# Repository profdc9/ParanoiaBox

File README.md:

# ParanoiaBox
The ParanoiaBox by Daniel L. Marks

The ParanoiaBox is a standalone open hardware/software encryption device based on the STM32F103CBT6 processor.  On this device, messages may be composed, encrypted, decrypted, and viewed.  The device is an experiment in encryption minimalism, presenting a minimal attack surface by using a small microcontroller rather than a full personal computer with a complex operating system, while providing the functionality needed to transact encrypted messages between humans through insecure networks.  The device is connected to a NTSC television and a PS/2 keyboard for user input and control.  There are two micro SD card slots, one for ciphertext and the other for plaintext used to transact files.  There is a hardware random number generator based on avalanche noise generated in two transistors.  A picture of the complete PCB of the device can be seen below:

At the top of the board is a RCA composite video connector.  At the right is a USB B connector that can be used to program the microcontroller.  At the lower right is a female PS/2 keyboard connector.  At the bottom are two SD card slots.  Finally, at the left is a barrel jack for 7 to 12 volt DC input power.  Except for the micro SD card slots, the PCB is all through assembly so it can be assembled more easily using simple tools.

The hardware is licensed under the Creative Commons CC-BY-SA 4.0 license.  The software written by D. L. Marks is licensed under the zlib license.  All other libraries are licensed under the licenses as described in the corresponding source files.  This hardware and software is provided under these licenses to be used at your own risk.  

THE HARDWARE AND SOFTWARE IS PROVIDED "AS IS", WITHOUT WARRANTY OF ANY KIND, EXPRESS OR IMPLIED, INCLUDING BUT NOT LIMITED TO THE WARRANTIES OF MERCHANTABILITY, FITNESS FOR A PARTICULAR PURPOSE AND NONINFRINGEMENT. IN NO EVENT SHALL THE AUTHORS OR COPYRIGHT HOLDERS BE LIABLE FOR ANY CLAIM, DAMAGES OR OTHER LIABILITY, WHETHER IN AN ACTION OF CONTRACT, TORT OR OTHERWISE, ARISING FROM, OUT OF OR IN CONNECTION WITH THE HARDWARE AND SOFTWARE OR THE USE OR OTHER DEALINGS IN THE HARDWARE AND SOFTWARE.

The project uses Advanced Encryption Standard AES256-GCM Galois Counter Mode as an authenticated symmetric encryption.  The keys are derived from shared secrets based on then Elliptic Curve Diffie-Hellmann (ECDH) 25519.  The keys are encrypted using a passphrase and AES256-GCM and stored in the flash memory of the microcontroller.  The encrypted data and public key certificates are base64 encoded so that they can be transmitted through e-mail as text files.  The library used is the Arduino Cryptography Library by Rhys Weatherley:

https://rweather.github.io/arduinolibs/crypto.html

The project uses the stm32duino libraries located here:

https://github.com/rogerclarkmelbourne/Arduino_STM32

All other Arduino libraries are provided in the libraries directory in this project, including those that provide the FAT fs, NTSC video output, PS/2 keyboard input, and cryptography.  To enter a message into the microcontroller, there is a full-screen text editor:

There is a the built-in full-screen editor used to compose short messages.  Files may be selected from the SD cards for editing, encryption, or decryption:

This is the key manager screen from which the AES 256 symmetric, ECDH25519 private or public keys are selected:

To encrypt/decrypt using AES, a AES key is selected.  To encrypt/decrypt using ECDH25519, a private and public key pair are selected.   Then one selects a file to encrypt or decrypt.  Separate SD cards must be used for encryption and decryption to ensure that both are not available together to be compared.  One can export a public key certificate from a private key.  After selection, the main screen shows the selected keys:

The message is then encrypted by selecting the file from the card in the plaintext slot using the (E)ncrypt option.  Then the encrypted file is placed on the card in the ciphertext slot.  You can view this file which is text encoded to be easily transmitted over email:

Once it has been received, it can be decrypted and viewed, and it looks like the original:

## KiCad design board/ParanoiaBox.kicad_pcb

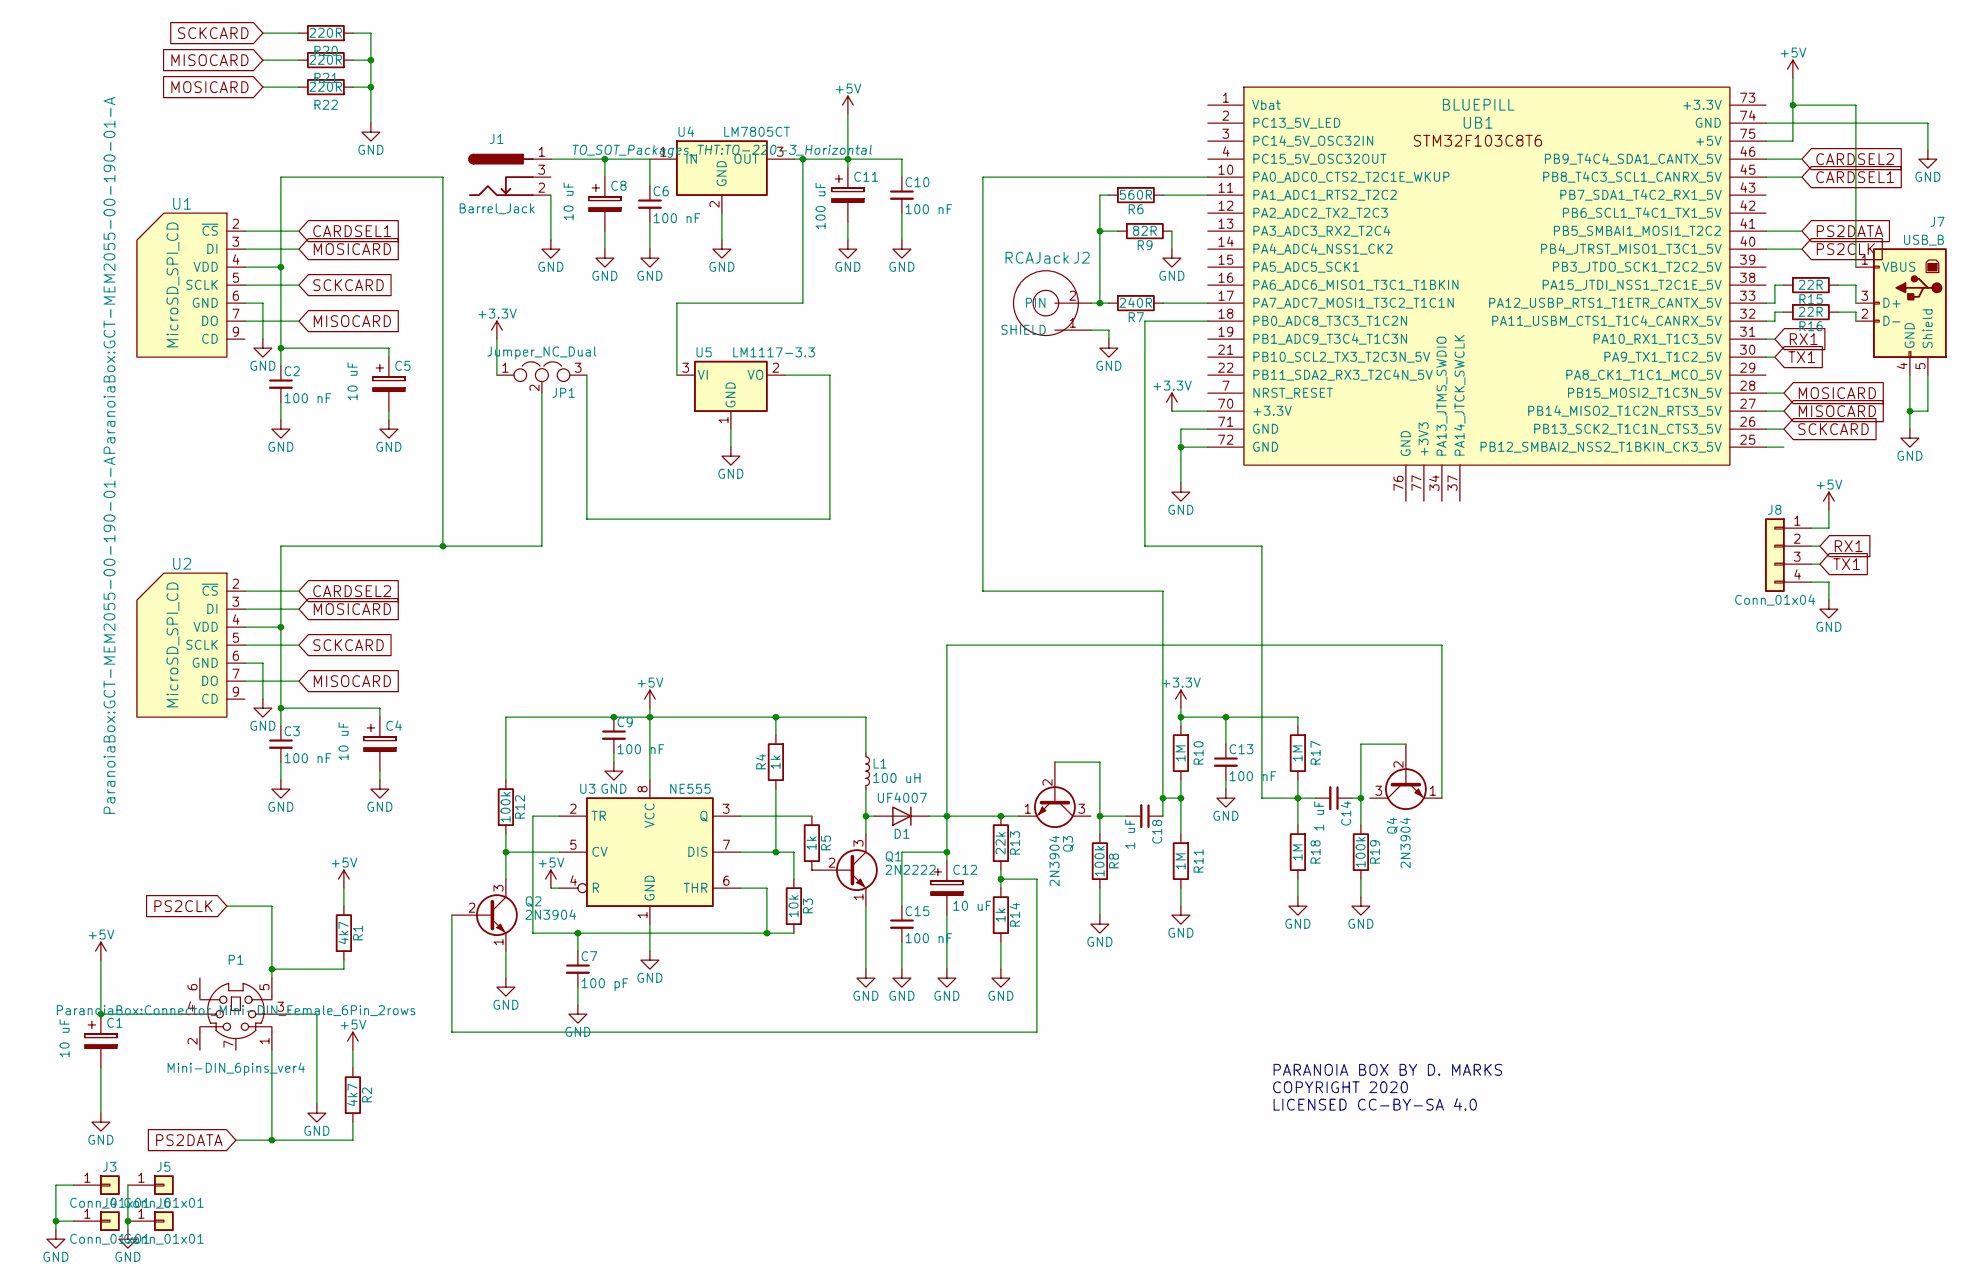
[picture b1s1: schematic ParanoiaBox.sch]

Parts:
C1, C4, C5, C8, C12: 10 uF; CP_Radial_D5.0mm_P2.50mm
C2, C3, C6, C9, C10, C13, C15: 100 nF; C_Disc_D5.0mm_W2.5mm_P2.50mm
C7: 100 pF; C_Disc_D5.0mm_W2.5mm_P2.50mm
C11: 100 uF; CP_Radial_D10.0mm_P5.00mm
C14, C18: 1 uF; C_Disc_D5.0mm_W2.5mm_P5.00mm
D1: UF4007; D_DO-41_SOD81_P7.62mm_Horizontal
J1: Barrel_Jack; BARREL_JACK
J2: RCAJack; RCAConnectorCommon
J3, J4, J5, J6: Conn_01x01; 1pin
J7: USB_B
J8: Conn_01x04; Pin_Header_Straight_1x04_Pitch2.54mm
JP1: Jumper_NC_Dual; Pin_Header_Straight_1x03_Pitch2.54mm
L1: 100 uH; L_Toroid_Horizontal_D5.1mm_P9.00mm_Diameter6-5mm_Amidon-T20
P1: Mini-DIN_6pins_ver4; Connector_Mini-DIN_Female_6Pin_2rows
Q1: 2N2222; TO-92_Inline_Wide
Q2, Q3, Q4: 2N3904; TO-92_Inline_Wide
R1, R2: 4k7; R_Axial_DIN0207_L6.3mm_D2.5mm_P7.62mm_Horizontal
R3: 10k; R_Axial_DIN0207_L6.3mm_D2.5mm_P7.62mm_Horizontal
R4, R5, R14: 1k; R_Axial_DIN0207_L6.3mm_D2.5mm_P7.62mm_Horizontal
R6: 560R; R_Axial_DIN0207_L6.3mm_D2.5mm_P7.62mm_Horizontal
R7: 240R; R_Axial_DIN0207_L6.3mm_D2.5mm_P7.62mm_Horizontal
R8, R12, R19: 100k; R_Axial_DIN0207_L6.3mm_D2.5mm_P7.62mm_Horizontal
R9: 82R; R_Axial_DIN0207_L6.3mm_D2.5mm_P7.62mm_Horizontal
R10, R11, R17, R18: 1M; R_Axial_DIN0207_L6.3mm_D2.5mm_P7.62mm_Horizontal
R13: 22k; R_Axial_DIN0207_L6.3mm_D2.5mm_P7.62mm_Horizontal
R15, R16: 22R; R_Axial_DIN0207_L6.3mm_D2.5mm_P7.62mm_Horizontal
R20, R21, R22: 220R; R_Axial_DIN0207_L6.3mm_D2.5mm_P7.62mm_Horizontal
U1, U2: MicroSD_SPI_CD; GCT-MEM2055-00-190-01-A
U3: NE555; DIP-8_W7.62mm_Socket
U4: LM7805CT; TO-220-3_Horizontal
U5: LM1117-3.3; TO-220-3_Horizontal
UB1: BLUEPILL

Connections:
+3V3: C13.1, JP1.1, R10.2, R17.2, UB1.70 (+3.3V)
+5V: C1.1, C9.1, C10.1, C11.1, J7.1 (VBUS), J8.1, L1.1, P1.4, R1.1, R2.1, R4.2, R12.1, U3.4 (R), U3.8 (VCC), U4.3 (OUT), U5.3 (VI), UB1.75 (+5V)
CARDSEL1: U1.2 (~CS), UB1.45 (PB8_T4C3_SCL1_CANRX_5V)
CARDSEL2: U2.2 (~CS), UB1.46 (PB9_T4C4_SDA1_CANTX_5V)
GND: C1.2, C2.2, C3.2, C4.2, C5.2, C6.2, C7.2, C8.2, C9.2, C10.2, C11.2, C12.2, C13.2, C15.2, J1.2, J2.1 (SHIELD), J3.1, J4.1, J5.1, J6.1, J7.4 (GND), J7.5 (Shield), J8.4, P1.3, Q1.1 (E), Q2.1 (E), R8.2, R9.1, R11.1, R14.2, R18.1, R19.2, R20.2, R21.2, R22.2, U1.6 (GND), U2.6 (GND), U3.1 (GND), U4.2 (GND), U5.1 (GND), UB1.71 (GND), UB1.72 (GND), UB1.74 (GND)
MISOCARD: R21.1, U1.7 (DO), U2.7 (DO), UB1.27 (PB14_MISO2_T1C2N_RTS3_5V)
MOSICARD: R22.1, U1.3 (DI), U2.3 (DI), UB1.28 (PB15_MOSI2_T1C3N_5V)
unnamed: C2.1, C3.1, C4.1, C5.1, JP1.2, U1.4 (VDD), U2.4 (VDD)
unnamed: C6.1, C8.1, J1.1, U4.1 (IN)
unnamed: C7.1, R3.2, U3.2 (TR), U3.6 (THR)
unnamed: C12.1, C15.1, D1.1 (K), Q3.1 (E), Q4.1 (E), R13.1
unnamed: C14.1, Q4.2 (B), R19.1
unnamed: C14.2, R17.1, R18.2, UB1.18 (PB0_ADC8_T3C3_T1C2N)
unnamed: C18.1, R10.1, R11.2, UB1.10 (PA0_ADC0_CTS2_T2C1E_WKUP)
unnamed: C18.2, Q3.2 (B), R8.1
unnamed: D1.2 (A), L1.2, Q1.3 (C)
unnamed: J2.2 (PIN), R6.2, R7.2, R9.2
unnamed: J7.2 (D-), R16.1
unnamed: J7.3 (D+), R15.1
unnamed: JP1.3, U5.2 (VO)
unnamed: Q1.2 (B), R5.2
unnamed: Q2.2 (B), R13.2, R14.1
unnamed: Q2.3 (C), R12.2, U3.5 (CV)
unnamed: R3.1, R4.1, U3.7 (DIS)
unnamed: R5.1, U3.3 (Q)
unnamed: R6.1, UB1.11 (PA1_ADC1_RTS2_T2C2)
unnamed: R7.1, UB1.17 (PA7_ADC7_MOSI1_T3C2_T1C1N)
unnamed: R15.2, UB1.33 (PA12_USBP_RTS1_T1ETR_CANTX_5V)
unnamed: R16.2, UB1.32 (PA11_USBM_CTS1_T1C4_CANRX_5V)
PS2CLK: P1.5, R1.2, UB1.40 (PB4_JTRST_MISO1_T3C1_5V)
PS2DATA: P1.1, R2.2, UB1.41 (PB5_SMBAI1_MOSI1_T2C2)
RX1: J8.2, UB1.31 (PA10_RX1_T1C3_5V)
SCKCARD: R20.1, U1.5 (SCLK), U2.5 (SCLK), UB1.26 (PB13_SCK2_T1C1N_CTS3_5V)
TX1: J8.3, UB1.30 (PA9_TX1_T1C2_5V)

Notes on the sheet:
PARANOIA BOX BY D. MARKS COPYRIGHT 2020 LICENSED CC-BY-SA 4.0

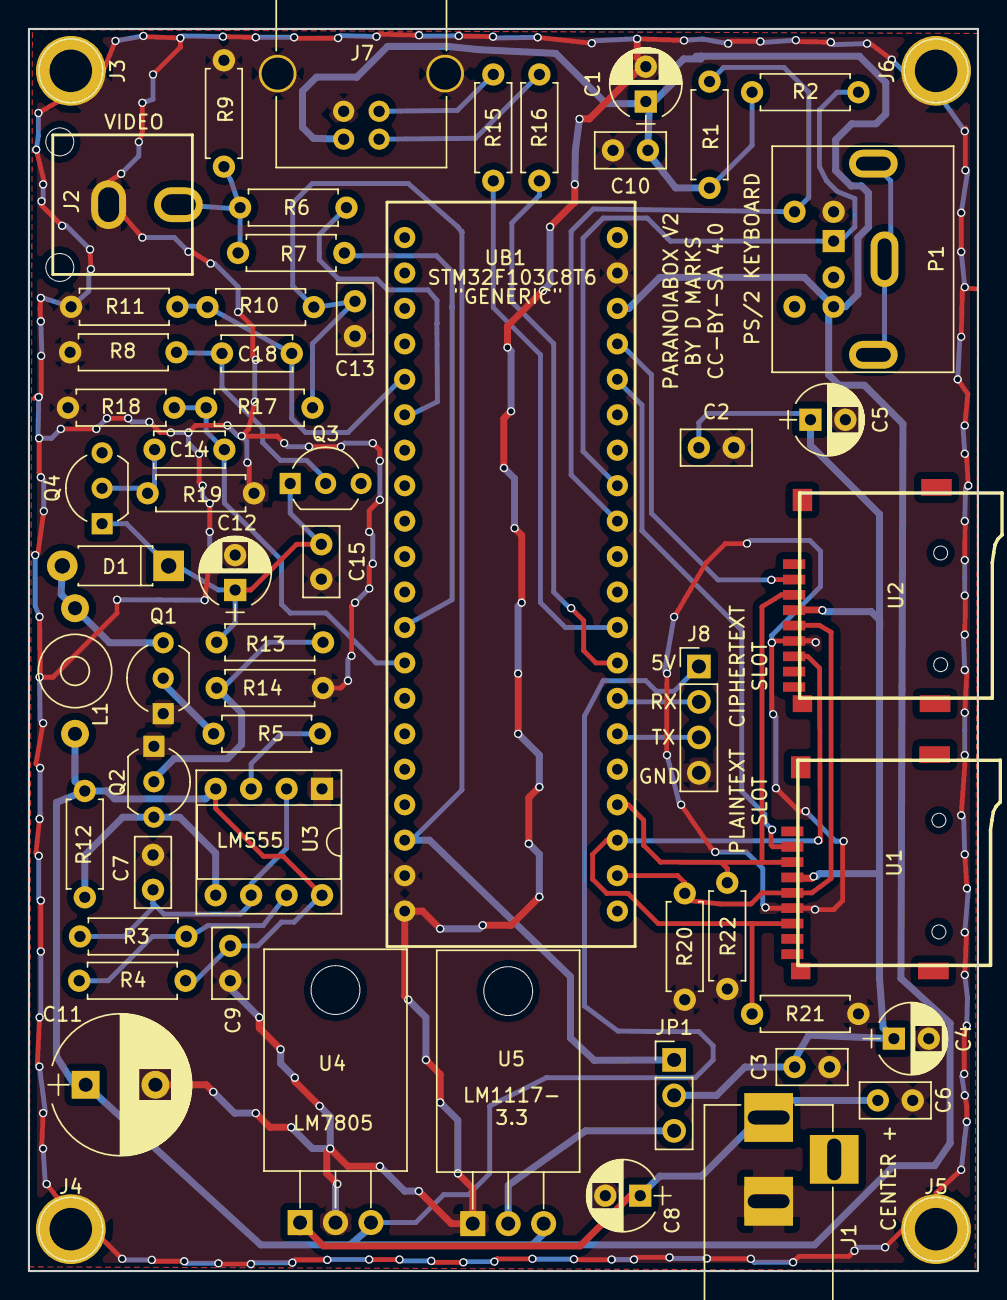
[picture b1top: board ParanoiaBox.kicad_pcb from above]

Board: 2 copper layers, 68.0 x 89.0 mm, 60 parts (0 on the bottom side), 34 nets.

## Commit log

2020-03-20 Added README file
2020-03-20 Added screenshot 3
2020-03-21 Changed key derivation function to PBKDF2/Blake2s (1000 iterations) and use HMAC rather than MAC for all of the hashes
2020-03-22 Changed from HMAC to the simpler AES256-GCM mode (as long as someone has implemented GCM for you)
2020-03-22 Moved iv2 into metadata structure to protect it from chosen ciphertext attack
2020-03-22 Change RNG back to standard RNG. Also added salt back to file key derivation
2020-03-22 Forgot to actually add SimpleTransistorNoiseSource
2020-03-22 PBKDF2 correction
2020-03-23 New screenshots
2023-06-28 Changed TNTSChar.cpp to have less flicker, board to use wide transistors
